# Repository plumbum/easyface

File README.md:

easyface
========

Simple LCD &amp; keyboard interface. Support RS232 or RS485

ModBus commands
---------------

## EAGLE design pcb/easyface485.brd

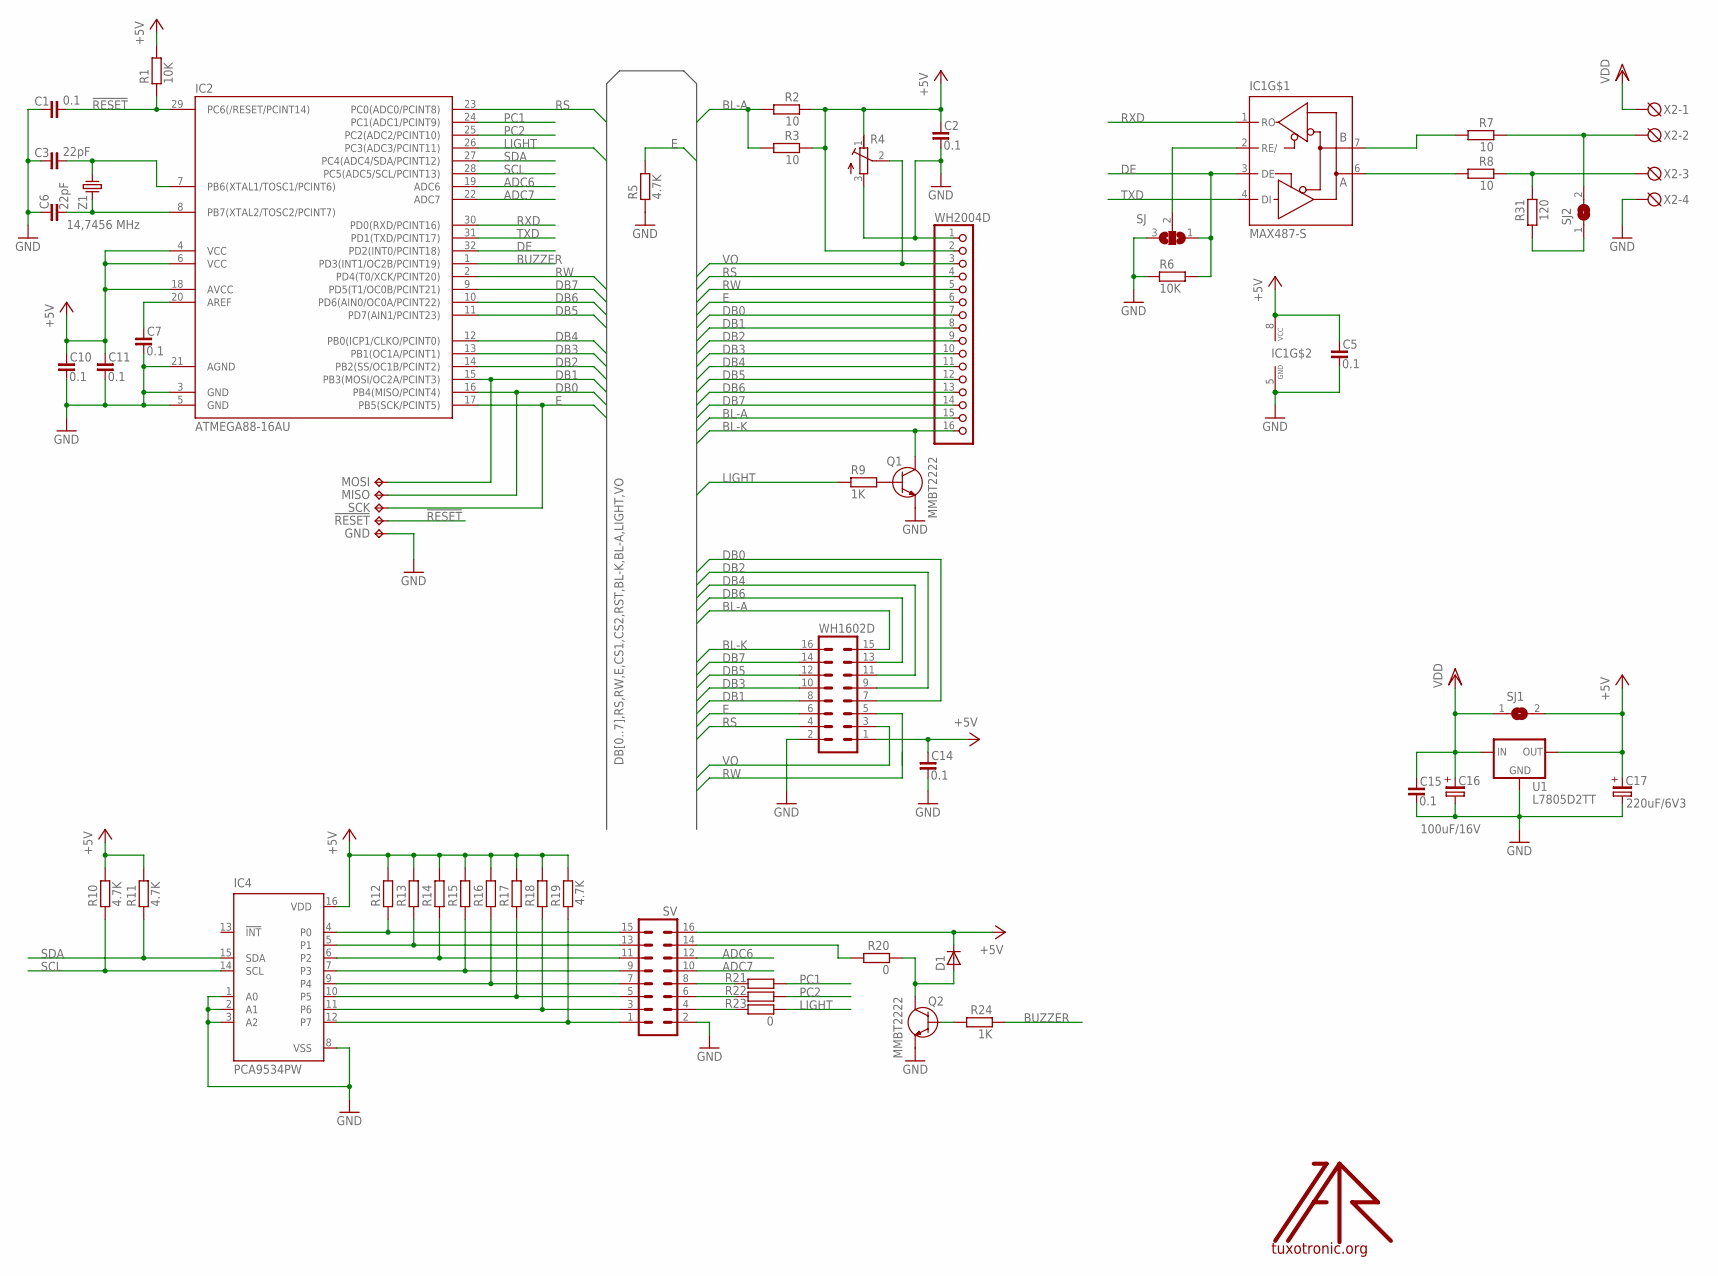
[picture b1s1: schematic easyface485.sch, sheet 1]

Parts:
!RESET: TPB1,27; B1,27
C1, C2, C5, C7, C10, C11, C14, C15: 0.1; C0805
C3, C6: 22pF; C0805
C16: 100uF/16V; SMC_D
C17: 220uF/6V3; SMC_D
D1: D-SOD-80; SOD80
GND: TPB1,27; B1,27
IC1: MAX487-S; SO08
IC2: ATMEGA88-16AU; TQFP32-08
IC4: PCA9534PW; SSOP16
MISO: TPB1,27; B1,27
MOSI: TPB1,27; B1,27
Q1, Q2: MMBT2222; SOT23
R1, R6: 10K; R0805
R2, R3, R7, R8: 10; R0805
R4: RTRIM; RTRIM-3362P
R5, R10, R11, R12, R13, R14, R15, R16, R17, R18, R19: 4.7K; R0805
R9, R24: 1K; R0805
R20, R21, R22, R23: 0; R0805
R31: 120; R0805
SCK: TPB1,27; B1,27
SJ: SJ2W; SJ_2
SJ1, SJ2: SJ
SV: ML16L
U1: L7805D2TT; D2PAK
U$: LOGO; TT_LOGO
WH1602D: MA08-2
WH2004D: PINHD-1X16_2.54-RND; 1X16RND
X2: DG3XX-04-3.5; DG350-3.5-04P
Z1: 14,7456 MHz; HC49/S

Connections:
!RESET: !RESET.PP, C1.2, IC2.29 (PC6(/RESET/PCINT14)), R1.1
+5V: C2.1, C5.1, C10.1, C11.1, C14.1, C17.+, D1.C, IC1.8 (VCC), IC2.4 (VCC), IC2.6 (VCC), IC2.18 (AVCC), IC4.16 (VDD), R1.2, R2.1, R3.1, R4.1 (A), R10.2, R11.2, R12.2, R13.2, R14.2, R15.2, R16.2, R17.2, R18.2, R19.2, SJ1.2, SV.16, U1.3 (OUT), WH1602D.1, WH2004D.2
ADC6: IC2.19 (ADC6), SV.12
ADC7: IC2.22 (ADC7), SV.10
BL-A: R2.2, R3.2, WH1602D.15, WH2004D.15
BL-K: Q1.3 (C), WH1602D.16, WH2004D.16
BUZZER: IC2.1 (PD3(INT1/OC2B/PCINT19)), R24.1
DB0: IC2.16 (PB4(MISO/PCINT4)), MISO.PP, WH1602D.7, WH2004D.7
DB1: IC2.15 (PB3(MOSI/OC2A/PCINT3)), MOSI.PP, WH1602D.8, WH2004D.8
DB2: IC2.14 (PB2(SS/OC1B/PCINT2)), WH1602D.9, WH2004D.9
DB3: IC2.13 (PB1(OC1A/PCINT1)), WH1602D.10, WH2004D.10
DB4: IC2.12 (PB0(ICP1/CLKO/PCINT0)), WH1602D.11, WH2004D.11
DB5: IC2.11 (PD7(AIN1/PCINT23)), WH1602D.12, WH2004D.12
DB6: IC2.10 (PD6(AIN0/OC0A/PCINT22)), WH1602D.13, WH2004D.13
DB7: IC2.9 (PD5(T1/OC0B/PCINT21)), WH1602D.14, WH2004D.14
DE: IC1.3 (DE), IC2.32 (PD2(INT0/PCINT18)), R6.2, SJ.1
E: IC2.17 (PB5(SCK/PCINT5)), R5.2, SCK.PP, WH1602D.6, WH2004D.6
GND: C1.1, C2.2, C3.1, C5.2, C6.1, C7.2, C10.2, C11.2, C14.2, C15.2, C16.-, C17.-, GND.PP, IC1.5 (GND), IC2.3 (GND), IC2.5 (GND), IC2.21 (AGND), IC4.1 (A0), IC4.2 (A1), IC4.3 (A2), IC4.8 (VSS), Q1.2 (E), Q2.2 (E), R4.3 (E), R5.1, R6.1, SJ.3, SV.2, U1.2 (GND), WH1602D.2, WH2004D.1, X2.4
LIGHT: IC2.26 (PC3(ADC3/PCINT11)), R9.1, R23.1
unnamed: R7.1, SJ2.2, X2.2
unnamed: IC4.4 (P0), R12.1, SV.15
unnamed: C7.1, IC2.20 (AREF)
unnamed: IC1.2 (RE/), SJ.2
unnamed: IC4.5 (P1), R13.1, SV.13
unnamed: Q2.1 (B), R24.2
unnamed: IC4.6 (P2), R14.1, SV.11
unnamed: R20.2, SV.14
unnamed: D1.A, Q2.3 (C), R20.1
unnamed: IC4.7 (P3), R15.1, SV.9
unnamed: Q1.1 (B), R9.2
unnamed: IC4.9 (P4), R16.1, SV.7
unnamed: IC4.10 (P5), R17.1, SV.5
unnamed: IC4.11 (P6), R18.1, SV.3
unnamed: IC4.12 (P7), R19.1, SV.1
unnamed: C3.2, IC2.7 (PB6(XTAL1/TOSC1/PCINT6)), Z1.2
unnamed: R8.1, R31.1, X2.3
unnamed: R21.2, SV.8
unnamed: R22.2, SV.6
unnamed: R23.2, SV.4
unnamed: R31.2, SJ2.1
unnamed: IC1.6 (A), R8.2
unnamed: IC1.7 (B), R7.2
PC1: IC2.24 (PC1(ADC1/PCINT9)), R21.1
PC2: IC2.25 (PC2(ADC2/PCINT10)), R22.1
RS: IC2.23 (PC0(ADC0/PCINT8)), WH1602D.4, WH2004D.4
RW: IC2.2 (PD4(T0/XCK/PCINT20)), WH1602D.5, WH2004D.5
RXD: IC1.1 (RO), IC2.30 (PD0(RXD/PCINT16))
SCL: IC2.28 (PC5(ADC5/SCL/PCINT13)), IC4.14 (SCL), R10.1
SDA: IC2.27 (PC4(ADC4/SDA/PCINT12)), IC4.15 (SDA), R11.1
TXD: IC1.4 (DI), IC2.31 (PD1(TXD/PCINT17))
VDD: C15.1, C16.+, SJ1.1, U1.1 (IN), X2.1
VO: R4.2 (S), WH1602D.3, WH2004D.3
XTAL2: C6.2, IC2.8 (PB7(XTAL2/TOSC2/PCINT7)), Z1.1

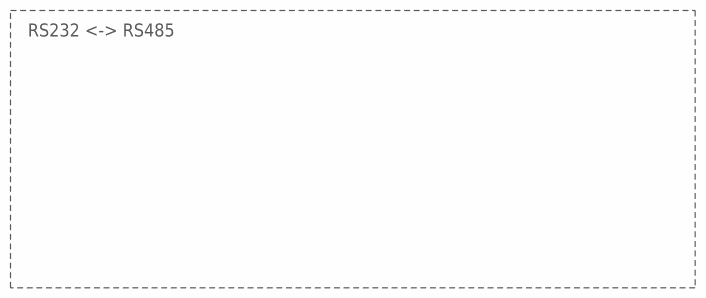
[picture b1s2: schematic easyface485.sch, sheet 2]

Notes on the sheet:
RS232 <-> RS485

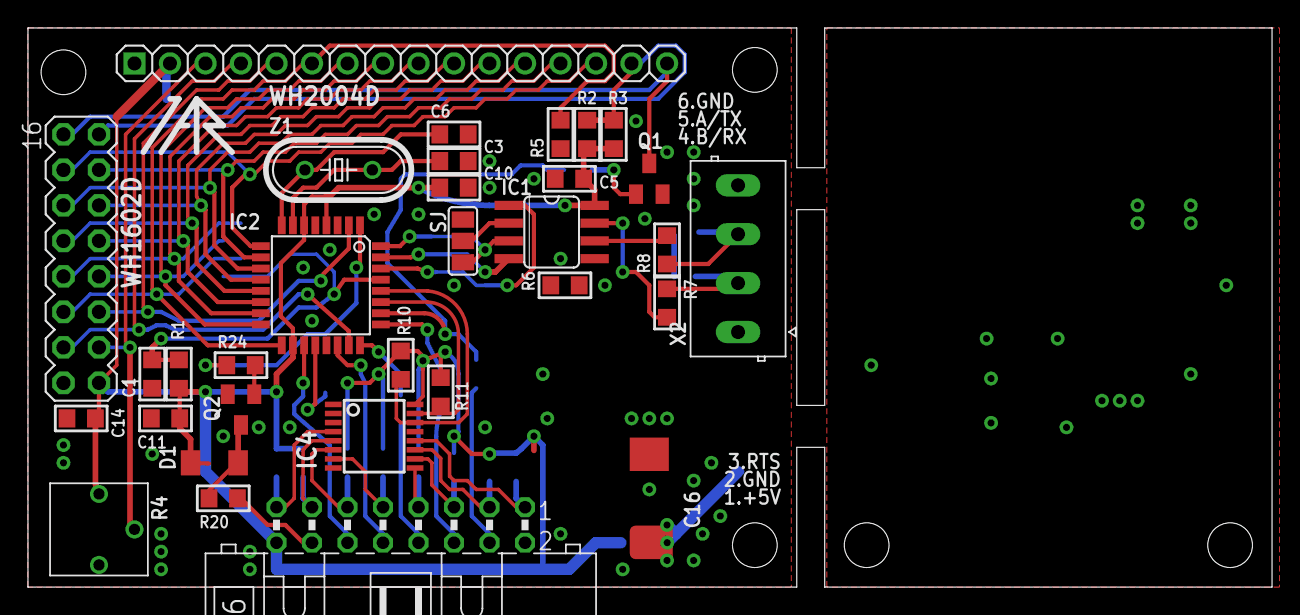
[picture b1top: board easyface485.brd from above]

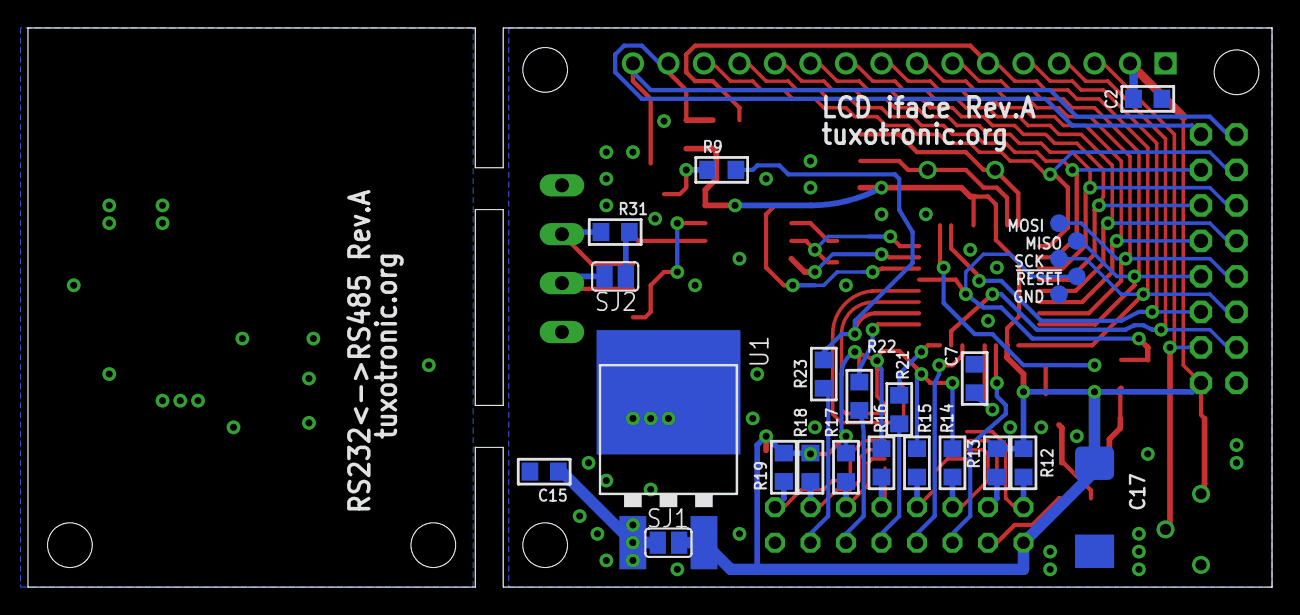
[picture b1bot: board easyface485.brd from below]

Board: 2 copper layers, 89.0 x 40.0 mm, 58 parts (25 on the bottom side), 53 nets.

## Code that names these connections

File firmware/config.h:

/*
 * =====================================================================================
 * 
 *       Filename:  config.h
 * 
 *    Description:  global configuration file
 * 
 *        Version:  1.0
 *        Created:  Fri Mar 14 17:46:40 MSK 2008
 *       Revision:  $Id$
 *       Compiler:  avr-gcc
 * 
 *         Author:  Ivan A-R <ivan@alferov.name>
 * 
 * =====================================================================================
 */

#ifndef  _CONFIG_H_
#define  _CONFIG_H_

#include <inttypes.h>
#include <avr/io.h>
#include <avr/wdt.h>
#include <avr/pgmspace.h>

#define WDT_EN 1

#define WRAPEN 1

#ifdef FALSE
#undef FALSE
#endif
#define FALSE (0)

#ifdef TRUE
#undef TRUE
#endif
#define TRUE (~FALSE)

#define PORT_SET(port, bits) { (port) |=  (bits); }
#define PORT_CLR(port, bits) { (port) &= ~(bits); }

#define _PIN(port, bit) ((port) & (1<<(bit)))
#define PIN(x) _PIN(x)

#define _PIN_SET(port, bit) do { *(volatile uint8_t*)((&port)+2) |=  (1<<(bit)); } while(0)
#define PIN_SET(x) _PIN_SET(x)

#define _PIN_CLR(port, bit) do { *(volatile uint8_t*)((&port)+2) &= ~(1<<(bit)); } while(0)
#define PIN_CLR(x) _PIN_CLR(x)

#define _PIN_TGL(port, bit) do { *(volatile uint8_t*)((&port)+2) ^= (1<<(bit)); } while(0)
#define PIN_TGL(x) _PIN_TGL(x)

#define _PIN_OUT(port, bit) do { *(volatile uint8_t*)((&port)+1) |=  (1<<(bit)); } while(0)
#define PIN_OUT(x) _PIN_OUT(x)

#define _PIN_IN(port, bit) do { *(volatile uint8_t*)((&port)+1) &= ~(1<<(bit)); } while(0)
#define PIN_IN(x) _PIN_IN(x)



/*
 * Pinout configuration
 */

#define BUZZER  PIND, PD2

#define RXD     PIND, PD0
#define TXD     PIND, PD1
#define DE      PIND, PD2

#define LCD_RS      PINC, PC0
#define LCD_E       PINB, PB5
#define LCD_WR      PIND, PD4

#define LCD_D0      PINB, PB4
#define LCD_D1      PINB, PB3
#define LCD_D2      PINB, PB2
#define LCD_D3      PINB, PB1
#define LCD_D4      PINB, PB0
#define LCD_D5      PIND, PD7
#define LCD_D6      PIND, PD6
#define LCD_D7      PIND, PD5

#define LIGHT       PINC, PC3
#define EXT6        PINC, PC2
#define EXT8        PINC, PC1


inline static void SET_DDR(void)
{
    PORTB = 0xFF;
    DDRB  = 0;
    PORTC = 0xFF;
    DDRC  = 0;
    PORTD = 0xFF;
    DDRD  = 0;

    PIN_CLR(DE);
    PIN_OUT(DE);
    PIN_CLR(LIGHT);
    PIN_OUT(LIGHT);
    PIN_CLR(LCD_E);
    PIN_OUT(LCD_E);
    PIN_OUT(LCD_RS);
    PIN_OUT(LCD_WR);

    /*
    PIN_CLR(EXT6);
    PIN_OUT(EXT6);
    PIN_CLR(EXT8);
    PIN_OUT(EXT8);
    uint8_t _PINB[2] = {0, 0xFF};
    uint8_t _PINC[2] = {0, 0xFF};
    uint8_t _PIND[2] = {0, 0xFF};

    VAR_PIN_CLR(DE);
    VAR_PIN_OUT(DE);
    VAR_PIN_CLR(LIGHT);
    VAR_PIN_OUT(LIGHT);
    VAR_PIN_CLR(LCD_E);
    VAR_PIN_OUT(LCD_E);
    VAR_PIN_OUT(LCD_RS);
    VAR_PIN_OUT(LCD_WR);

    PORTB = _PINB[0];
    DDRB  = _PINB[1];
    PORTC = _PINC[0];
    DDRC  = _PINC[1];
    PORTD = _PIND[0];
    DDRD  = _PIND[1];
    */
}

#define CYCLES_PER_US ((F_CPU+500000)/1000000) 	// cpu cycles per microsecond

#define _B(x) (1<<(x))

#define _SB(x) |= _B(x)
#define _RB(x) &= ~(_B(x))

#define _SET(x, val, msk) (x) = (val | ((x) & ~(msk)))

#define HI(x) (uint8_t)((x)>>8)
#define LO(x) (uint8_t)((x) & 0xFF)

#define NOP __asm__ __volatile__ (" nop ")

#ifdef WDT_EN
#   define wdr() wdt_reset()
#else
#   define wdr()
#endif

void egpio_systimer(void);


#define delay() do { \
    volatile uint8_t __i; \
    for(__i=0; __i<20; __i++) {} \
} while(0)
#endif   /* ----- #ifndef _CONFIG_H_  ----- */

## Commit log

2012-12-04 easyface sch & pcb. lcd controller
2012-12-05 lcd board in progress
2012-12-06 ready to resonit
2012-12-06 cam processing
2013-04-06 base functions
2013-04-06 timer
2013-04-07 timer 1khz test
2013-04-08 uart rx timeout
2013-04-08 modbus skel
2013-04-24 systimer
2013-04-24 modbus in progress
2013-04-28 I2C interrupt driving
2013-06-15 Vim formatting
2013-06-15 Keyboard scancodes
2013-06-15 Modbus keyboard reader
2013-06-15 test routine
2013-06-15 test read scancodes & print result
2013-06-19 RS485 only
2013-06-20 new pcb in progress
2013-06-20 some config registers
